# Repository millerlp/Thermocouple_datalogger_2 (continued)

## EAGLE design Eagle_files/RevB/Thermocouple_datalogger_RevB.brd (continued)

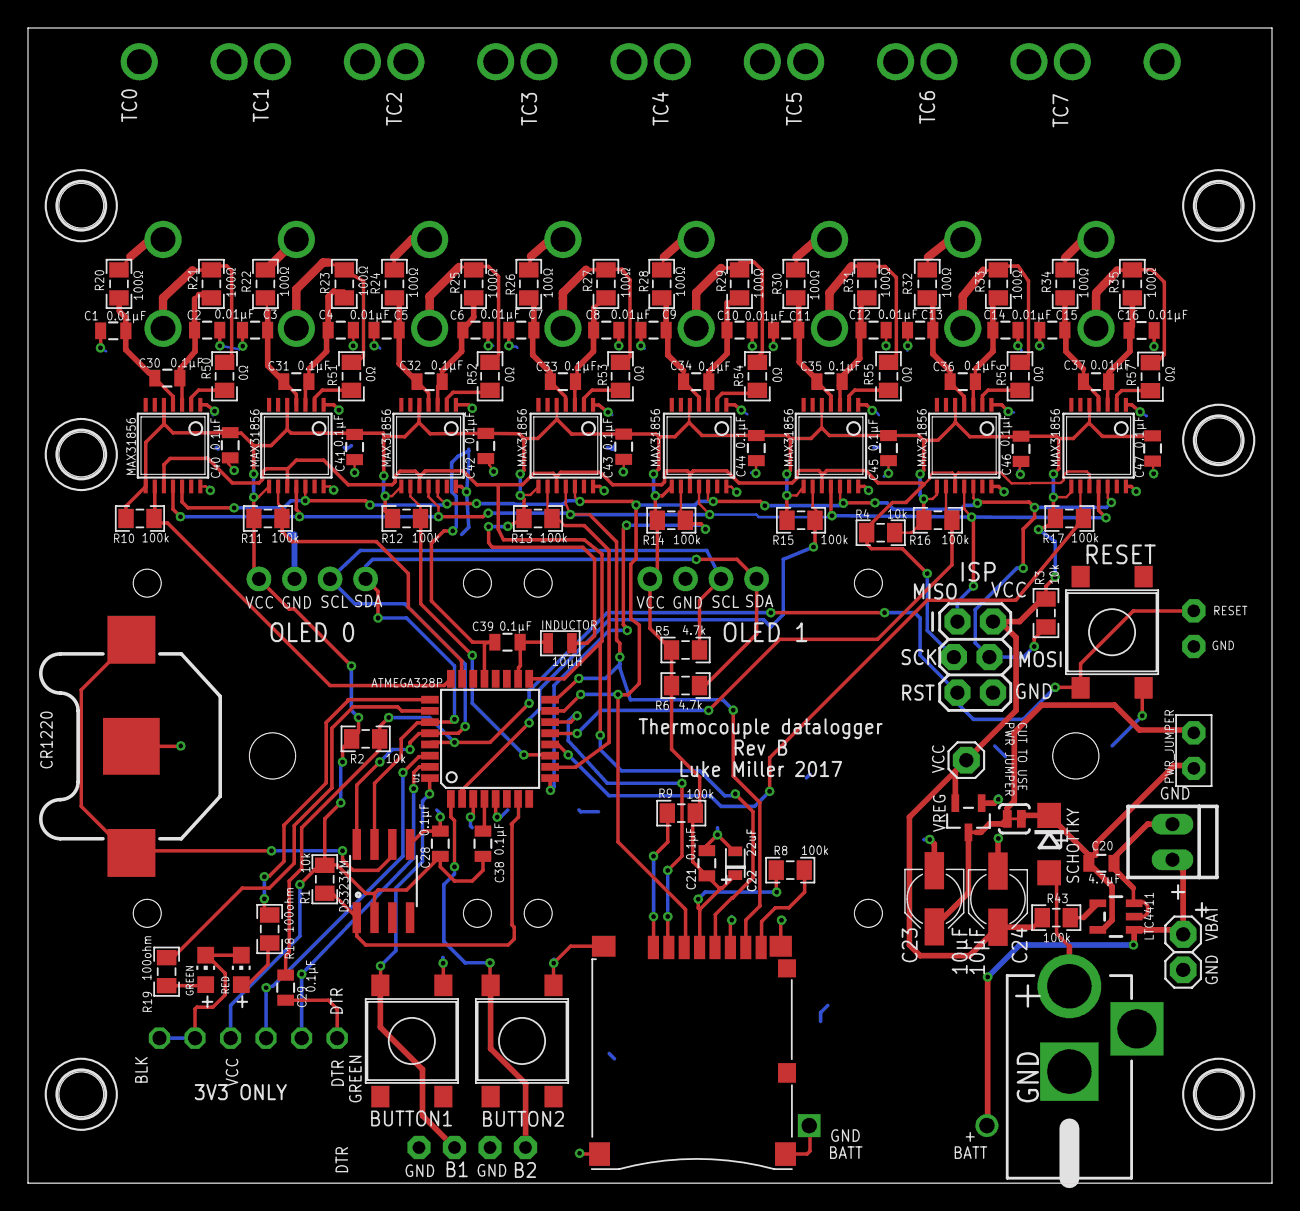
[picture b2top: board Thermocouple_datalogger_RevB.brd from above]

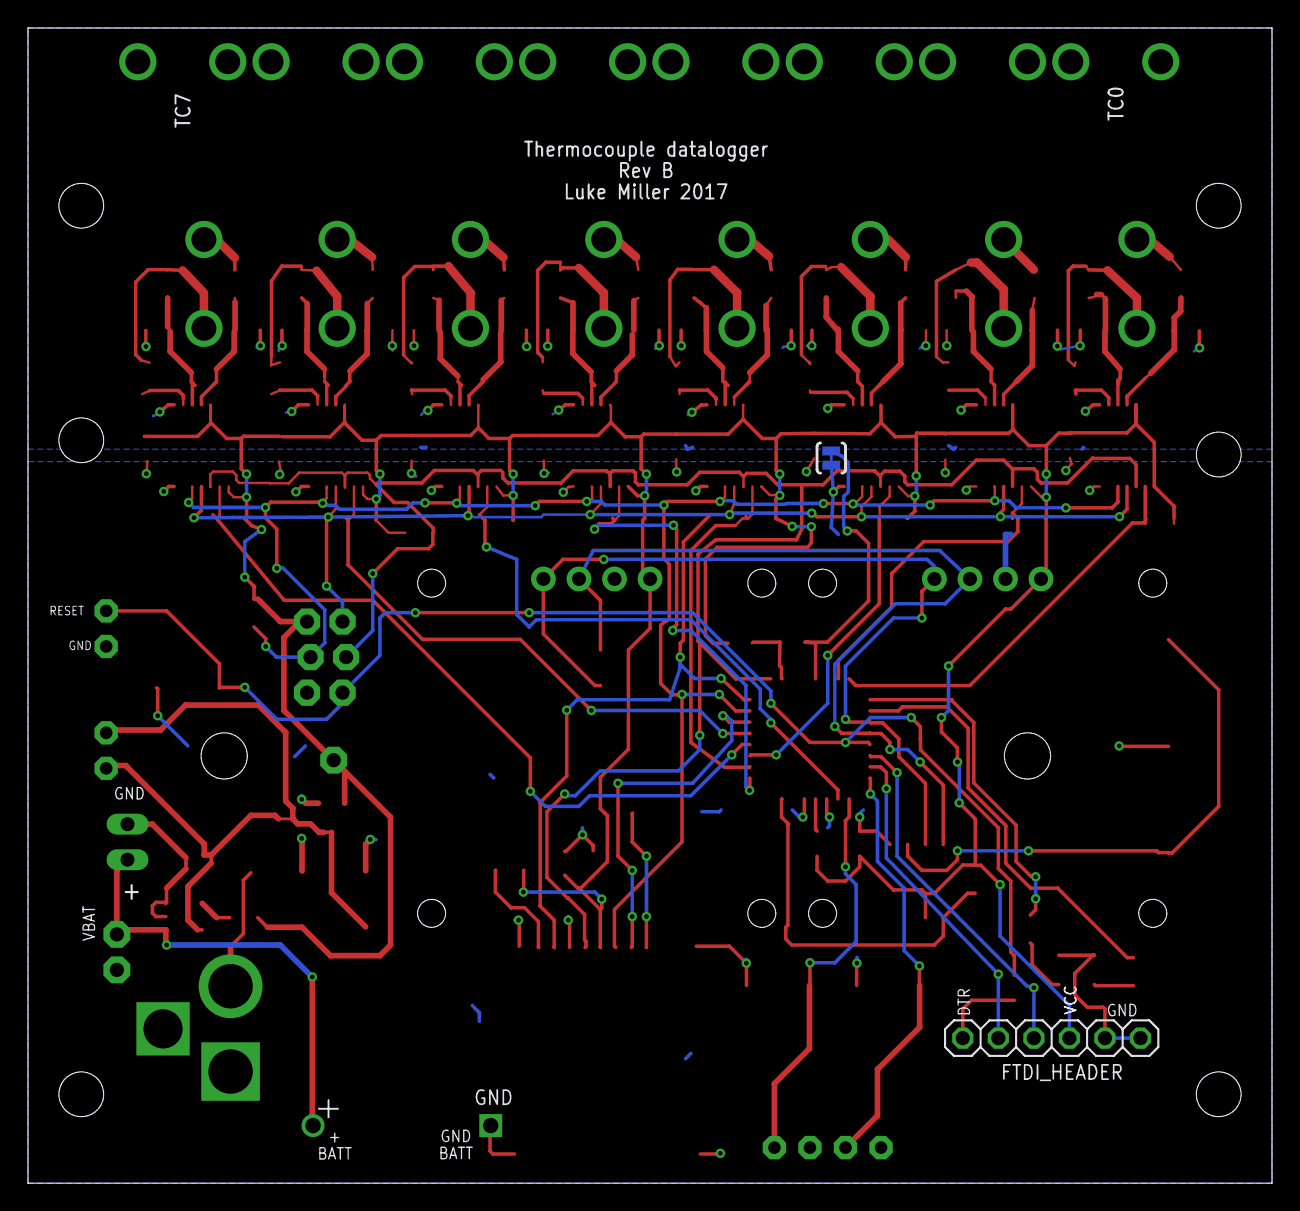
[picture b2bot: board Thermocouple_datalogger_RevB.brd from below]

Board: 2 copper layers, 88.9 x 82.5 mm, 135 parts (3 on the bottom side), 78 nets.

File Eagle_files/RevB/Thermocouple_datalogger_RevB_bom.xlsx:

Qty | Value | Device | Package | Parts | Description
2 |  | PUSHBUTTON_DPST_SMDSTANDARD | PUSHBUTTON_DPST_SMD | BUTTON1, BUTTON2 | PUSHBUTTON DPST SMD
17 | 0.01µF | CAP0805 | 805 | C1, C2, C3, C4, C5, C6, C7, C9, C10, C11, C12, C13, C14, C15, C16, C17, C37 | Capacitor
20 | 0.1µF | CAP0805 | 805 | C30, C31, C32, C33, C34, C35, C36, C40, C41, C42, C43, C44, C45, C46, C47, C48,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 | Capacitor
8 | 0O | RESISTOR_SMDR0805 | R0805 | R7, R24, R27, R30, R33, R36, R39, R42 | RESISTOR, American symbol
11 | 100k | RESISTOR_SMDR0805 | R0805 | R10, R11, R12, R13, R14, R15, R16, R17, R18, R19, R43 | RESISTOR, American symbol
2 | 100ohm | RESISTOR_SMDR0805 | R0805 | R8, R9 | RESISTOR, American symbol
16 | 100O | RESISTOR_SMDR0805 | R0805 | R5, R6, R22, R23, R25, R26, R28, R29, R31, R32, R34, R35, R37, R38, R40, R41 | RESISTOR, American symbol
4 | 10k | RESISTOR_SMDR0805 | R0805 | R1, R2, R20, R21 | RESISTOR, American symbol
2 | 10µF | CPOL-USB | PANASONIC_B | C23, C24 | POLARIZED CAPACITOR, American symbol
1 | 10µH | INDUCTOR0805_TY | I_0805 | INDUCTOR | Inductor
1 | 22-23-2021 | 22-23-2021 | 22-23-2021 | VIN_KK | Molex KK series
1 | 22uF | CPOL-US0805 | C0805_POL | C8 | POLARIZED CAPACITOR, American symbol
2 | 4.7k | RESISTOR_SMDR0805 | R0805 | R3, R4 | RESISTOR, American symbol
1 | 4.7µF | CAP0805 | 805 | C18 | Capacitor
1 | ATMEGA328P | ATMEGA328_SMT | TQFP32-08 | U1 | 32-Pin Atmega328
1 | AVR_SPI_PRG_62X3_LOCK | AVR_SPI_PRG_62X3_LOCK | 2X3_LOCK | J1 | AVR ISP 6 Pin
1 | BATTERY_4XAA | BATTERY_4XAA | BATTERY_4XAA_PTH | U$18 | Battery holder 4xAA
1 | CR1220_BATTERY_HOLDERSMD | CR1220_BATTERY_HOLDERSMD | CR1220_BATTERY_HOLDER_SMD | CR1220_BATTERY | CR1220 Battery Holder
1 | DS3231MSOIC-8 | DS3231MSOIC-8 | DS3231M_SOIC8 | DS3231M | DS3231M real time clock
1 | FTDI_HEADER | PINHD-1X6RA | 1X06-RIGHT_ANGLE | JP1 | PIN HEADER
1 | GREEN | LED0805 | CHIPLED_0805 | LED2 | LEDs
6 | HOLE-LAYOUT4-40-SOCKET-HEAD | HOLE-LAYOUT4-40-SOCKET-HEAD | 4-40-SCREW-HOLE | U$6, U$15, U$16, U$23, U$24, U$25 | Drill hole
1 | JACK_2,1MM | POWER_JACK_2,1MM | POWER_JACK_DC_2,1MM | U$2 | DC Power Jack, 2.1mm center pin.
1 | LTC4411TSOT-23_5-LEAD | LTC4411TSOT-23_5-LEAD | TSOT-23_5-LEAD | LTC4411 | 2.6A Low Loss Ideal diode in ThinSOT
8 | MAX31856 | MAX31856 | MAX31856_TSSOP14 | MAX0, MAX1, MAX2, MAX3, MAX4, MAX5, MAX6, MAX7 | MAX31856 Thermocouple convertor
1 | MCP1700T-3302E/TT | MCP1700T-3302E/TT | SOT95P237X112-3N | U$7 | Low Quiescent Current LDO
1 | MICROSD_MOLEX_REVERSECURRENT | MICROSD_MOLEX_REVERSECURRENT | MICROSD_SOCKET_MOLEX_REVERSEMOUNT | U$5 | Molex micro SD connector, push-push spring loaded, reverse" mount"
2 | OLED_0.96_I2CWIDE | OLED_0.96_I2CWIDE | OLED_0.96_I2C_VCC_PIN1_WIDE | OLED_0, OLED_1 | CHECK VCC & GND PIN VARIANT
8 | PCC-SMP-THERMOCOUPLEVERTICAL | PCC-SMP-THERMOCOUPLEVERTICAL | PCC-SMP-V | TC0, TC1, TC2, TC3, TC4, TC5, TC6, TC7 | PCC-SMP
3 | PINHD-1X1STANDARD | PINHD-1X1STANDARD | 1X01 | TP_GND, TP_VBAT, VCC | Just a single pin header, useful for making test point or stand-alone header ho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
3 | PINHD-1X2NOSILK | PINHD-1X2NOSILK | 1X02_NOSILK | TP_BUTTON1, TP_BUTTON2, TP_RESET | 1x2 pin header 0.1 spacing (2.54mm)"
1 | PUSHBUTTON_SMD | PUSHBUTTON_DPST_SMDSTANDARD | PUSHBUTTON_DPST_SMD | RESET_BUTTON | PUSHBUTTON DPST SMD
1 | RED | LED0805 | CHIPLED_0805 | LED1 | LEDs
1 | SCHOTTKY_DIODE_DO-214AC | SCHOTTKY_DIODE_DO-214AC | DO214AC | SCHOTTKY | Schottky diode
1 | SOLDER_JUMPER_TRACESTANDARD | SOLDER_JUMPER_TRACESTANDARD | SJ_2S-TRACE | AGND-GND-CON | Solder jumper with trace

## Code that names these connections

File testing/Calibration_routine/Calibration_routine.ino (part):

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
#define ERRLED A2    // Red error LED pin
#define GREENLED A3   // Green LED pin
#define BUTTON1 2     // BUTTON1 on INT0, pin PD2
#define BUTTON2 3     // BUTTON2 on INT1, pin PD3
//*********************
#define SAMPLES 5    // number of samples per temperature
//*********************
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const byte chipSelect = 10; // define the Chip Select pin for SD card

// Define MAX31855 objects, need 8 of them for the 8 separate chips
#define CS_MAX0 A1 // Arduino pin PC1, analog 1, Chip Select for MAX31855 #0
#define CS_MAX1 A0 // Arduino pin PC0, analog 0, Chip Select for MAX31855 #1
#define CS_MAX2 7 // Arduino pin PD7, digital 7, Chip Select for MAX31855 #2
#define CS_MAX3 6 // Arduino pin PD6, digital 6, Chip Select for MAX31855 #3
#define CS_MAX4 5 // Arduino pin PD5, digital 5, Chip Select for MAX31855 #4
#define CS_MAX5 4 // Arduino pin PD4, digital 4, Chip Select for MAX31855 #5
#define CS_MAX6 9 // Arduino pin PB1, digital 9, Chip Select for MAX31855 #6
#define CS_MAX7 8 // Arduino pin PB0, digital 8, Chip Select for MAX31855 #7

Adafruit_MAX31855 thermocouple0(CS_MAX0);
Adafruit_MAX31855 thermocouple1(CS_MAX1);
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 
void setup() {
  // Set button1 as an input
  pinMode(BUTTON1, INPUT_PULLUP);
  // Set button2 as an input
  pinMode(BUTTON2, INPUT_PULLUP);
    // Set up the LEDs as output
  pinMode(ERRLED,OUTPUT);
  digitalWrite(ERRLED, LOW);
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  digitalWrite(GREENLED, LOW);
  // Set the SPI bus chip select pins as outputs
  // for the MAX31855 thermocouple chips
  pinMode(CS_MAX0, OUTPUT);
  digitalWrite(CS_MAX0, HIGH);
  pinMode(CS_MAX1, OUTPUT);
  digitalWrite(CS_MAX1, HIGH);
  pinMode(CS_MAX2, OUTPUT);
  digitalWrite(CS_MAX2, HIGH);
  pinMode(CS_MAX3, OUTPUT);
  digitalWrite(CS_MAX3, HIGH);
  pinMode(CS_MAX4, OUTPUT);
  digitalWrite(CS_MAX4, HIGH);
  pinMode(CS_MAX5, OUTPUT);
  digitalWrite(CS_MAX5, HIGH);
  pinMode(CS_MAX6, OUTPUT);
  digitalWrite(CS_MAX6, HIGH);
  pinMode(CS_MAX7, OUTPUT);
  digitalWrite(CS_MAX7, HIGH);
  // Flash green LED to show that we just booted up
  for (byte i = 0; i < 3; i++){
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
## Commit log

2017-06-04 :circus_tent: Added .gitattributes & .gitignore files
2017-06-04 Initial commit - testing only
2017-06-05 Fixing comment marker
2017-06-05 Functional test prototype with 2 OLED screens, RTC, buttons etc.
2017-06-05 Adding comments at the start
2017-06-06 Non-tested, probably not functional prototype program
2017-06-06 Mostly functional basic datalogger
    TODOs: implement button functions, sleep screens, refine screen refresh,
    implement moving average of temperatures
2017-06-06 Moving most functions over to TClib2 library
2017-06-06 Mostly broken
2017-06-06 Still broken
2017-06-06 Currently appears functional. Added separate data saving interval and sampling interval, with moving average window
2017-06-07 Simple test of clearing and overwriting sections of OLED display
2017-06-07 Added code to only clear and update certain sections of OLED screen.
2017-06-07 Moving OLED update code to the TClib2 library
2017-06-07 Cleaning up OLED update code, adding TODOs
2017-06-07 Resolving conflicts, updating from branch tempArrayMod
2017-06-07 Resolving last conflict, functional prototype now
2017-06-07 Adding delay at start so that recordings are on nice even time stamps like 0 or 5 seconds instead of 1 and 6 seconds
2017-06-08 Adding calibration program
2017-06-08 Updated routine to just automatically set next test temperature
2017-06-08 Switched to all onboard control
    Uses the buttons and OLED screens to let the user calibrate, without the
    need for a serial connection.
2017-06-14 Adding temperature output to wait screen, and internal temperature on wait screen as well.
2017-06-14 Adding in code to use NIST-corrected temperature output from the MAX31855 chips. Saved data now reflect this corrected value rather than the raw temperature value coming directly from the MAX31855.
2017-06-15 Switching over to using MAX31855K_NIST library
    The new library makes use of simultaneously measured internal and
    external temperatures of the MAX31855K and implements a linearization
    using the NIST K-type polynomial and coefficients.
2017-06-15 Adding github link to MAX31855K_NIST library
2017-06-15 Switching to MAX31855K_NIST library
2017-06-15 Adding in calibration offsets for all 8 channels, based on calibrations carried out on 2017-06-14 and 15 with RevA Board 1.
2017-06-15 Applying calibration corrections to the incoming temperature values individually, using pooled calibration data coefficients.
2017-06-15 Handling missing SD card, gives user ability to run without card
2017-06-15 Functional data collection routine, with calibration coefficients.
2017-08-11 Moving RevA code to titled folders
    RevB has arrived, so it's time for the older RevA code to go live in
    special folders and get the mark of the RevA beast tattooed on the file
    names.
2017-08-11 Also renaming these as RevA code
2017-08-11 Updated to show compatability with RevA + RevB
2017-08-11 Reverting to old name since RevA + RevB hardware both work
2017-08-11 Working as expected with 4 channels
2017-08-11 Functional on RevB hardware
2017-08-11 Currently having problems, registering no MAX31856
    There's some kind of issue with the MAX31856, possibly because the SdFat
    library is also trying to use the SPI lines now?
2017-08-11 This works fine with 8 channels
2017-08-11 Still returning NO_MAX31856 for some reason
    Has to be an issue with SdFat.
2017-08-11 Minimal working version, single channel using Adafruit lib
2017-08-11 First test, works fine for one channel on RevB board
2017-08-12 Basic working calibration routine with 8 channels
2017-08-12 Moving this into the proper folder
2017-08-12 Updating to forked version of Adafruit_MAX31856 library
2017-08-12 Modified version for RevB hardware. Initial tests
2017-08-12 Program to store individual MAX31856 calibration slope and offset values in the board's EEPROM memory
2017-08-12 Testing code to read/write calibration values from EEPROM
2017-08-12 Moving EEPROM read/write functions to TClib2 librar
2017-08-12 Adding routing to read calibration offset and slope values from EEPROM at startup, or use default values (0.00, 1.00) if none are present in EEPROM.
2017-08-13 Only clearing relevant memory space
    No need to clear out all EEPROM if we're only going to write 16 float
    values to the start of the EEPROM address space, so I'm cutting this
    down to just clear out those addresses.
2017-08-13 Adding some sanity checking to readout values
    Make sure the values being read back out of the EEPROM are within
    0.00001 of the original values being written to EEPROM. This should
    always be true in this program, but it doesn't hurt to check.
2017-08-13 Adding explanation to comments
2017-08-13 Formatting comments
2017-08-13 Adding sanity checking to the EEPROM values
    Calibration values read out from the EEPROM should be sanity checked to
    make sure they are within semi-reasonable bounds. The offset (intercept)
    value may deviate a couple of degrees from the factory, so we set a wide
    range of +/- 3. The slope range is restricted to 0.5 to 1.5 by this
    code, and we really ought to expect a slope very close to 1.0. If
    calibrations values are outside these bounds, either the EEPROM values
2017-08-13 Updating to read calibration from EEPROM
    Use the separate program Store_calibrations.ino to write the 8 channel
    calibration slope + offset values into EEPROM for a particular board.
    This modification will then read those values out of EEPROM and use
    them. This removes the need to alter this main program every time you
    want to program a different board that has its own calibration
    coefficients.
2017-08-13 Moving Serial print messages to PROGMEM
2017-08-13 Ignore me
2017-08-13 Naming for loop variables more explicitly
2017-08-13 Adding future TODO tasks
2017-08-13 More details on button press actions
2017-08-13 Putting a README file together, 1st draft.
2017-08-13 Formatting the library list, adding more info
2017-08-13 Let's be honest here.
2017-08-13 Moving board design files over
2017-08-13 Adding details about parts and design files
2017-08-13 Adding some images
2017-08-13 Fixing links
2017-08-13 Adding board picture
2017-08-22 Updating to store new calibs
2017-08-22 Writing a little test program to make sure math and calibrations are being applied properly
2017-08-22 Cleaning out older cruft, adding in a new column of output data holding cold junction temperatures
2017-08-22 Making the loop end at NUM_MAX31856 instead of hard-coded 8, also printing more digits for the calibration coefficient readout
2017-08-25 Updating calibs
2018-12-07 spelling!
2021-07-19 Updating clock check
2023-03-06 Update clock check
2023-03-15 Removing Button 2, but this didn't fix things with the busted board
2024-02-15 Catching up to new use of RTClib toString() function
2024-02-16 Updating time printout via toString() function
    RTClib changed a while back, and the toString() function changed as a result, so this should fix the various places where it's used to print out the date and time.
